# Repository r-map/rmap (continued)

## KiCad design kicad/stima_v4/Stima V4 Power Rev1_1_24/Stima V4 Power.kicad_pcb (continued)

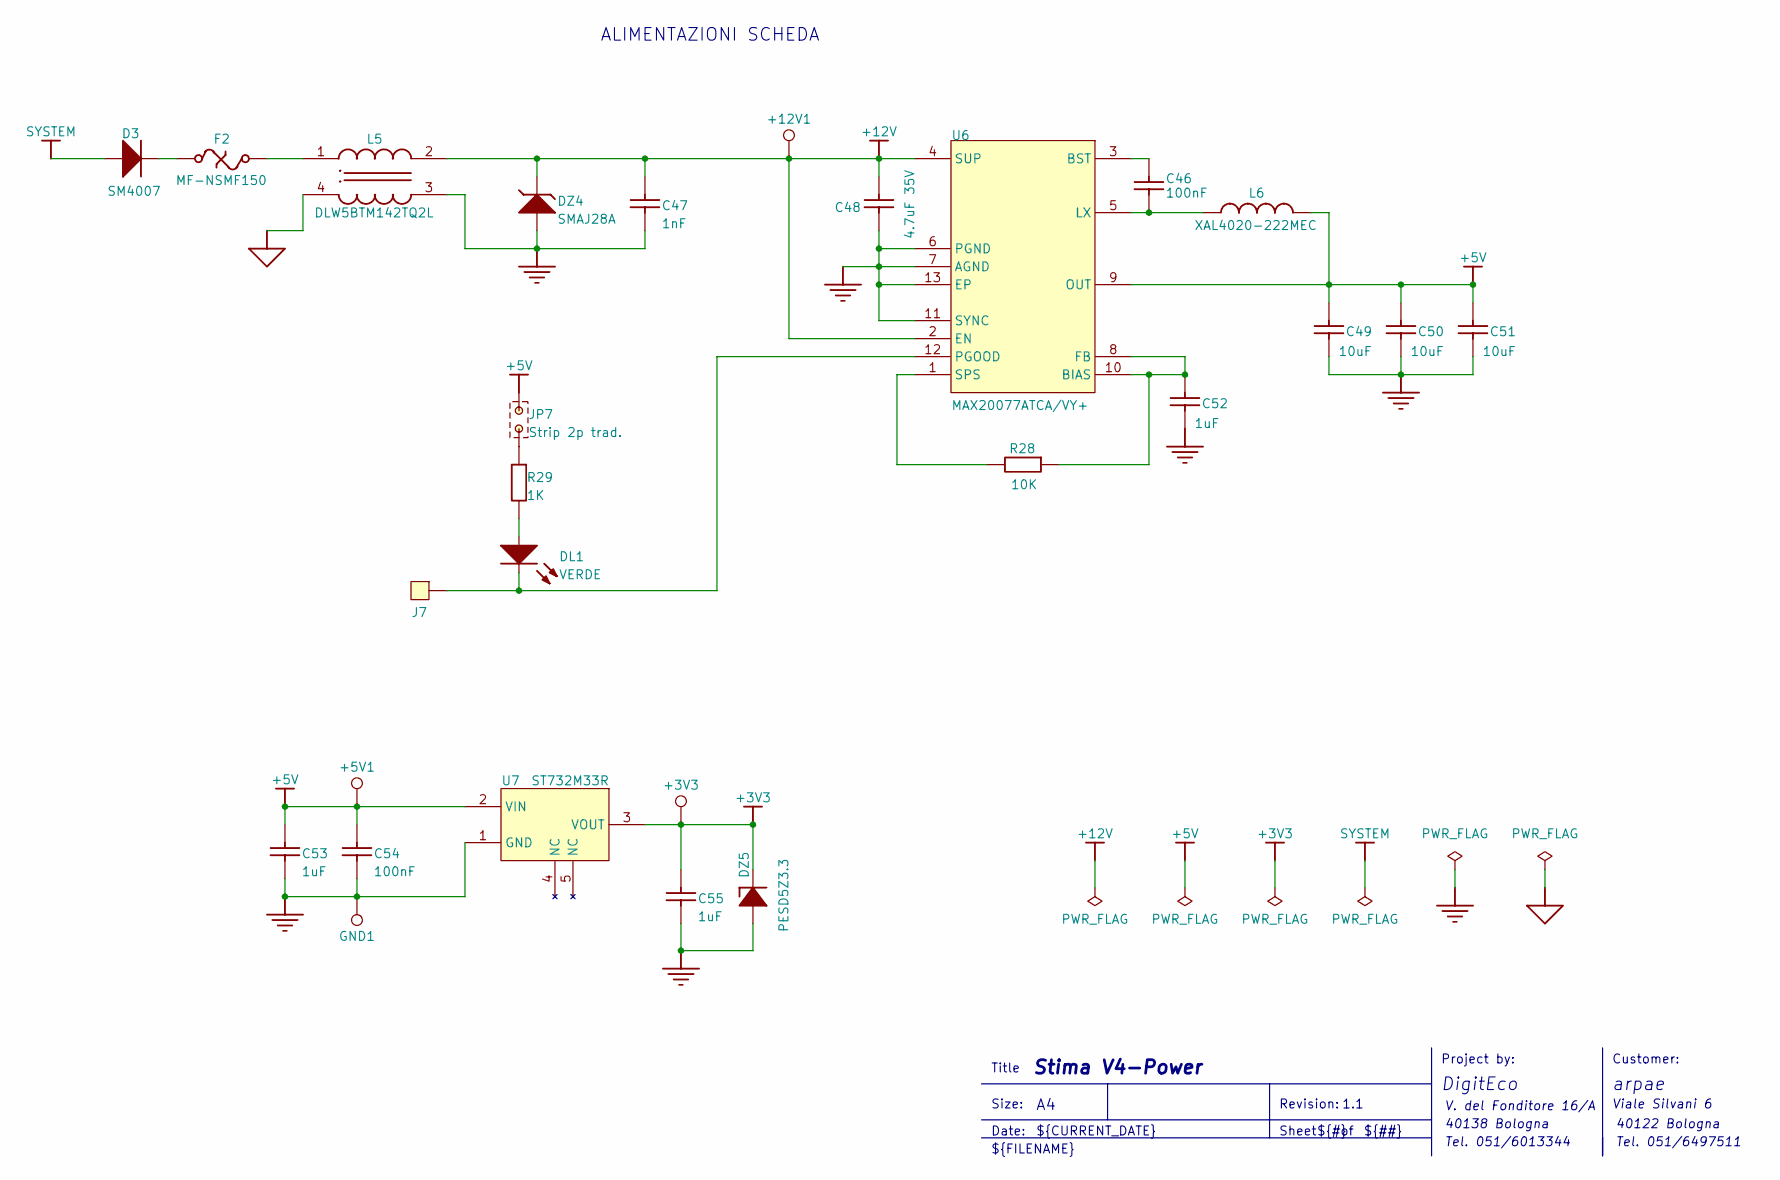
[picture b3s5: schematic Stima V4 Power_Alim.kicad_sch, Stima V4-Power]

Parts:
+3V3, +5V1, +12V1: TestPoint; TP
C46, C54: 100nF; 0603; VOLTAGE 50V
C47: 1nF; 0603; VOLTAGE 50V
C48: 4.7uF 35V; 1206; VOLTAGE 35V
C49, C50, C51: 10uF; 0603; VOLTAGE 20V
C52: 1uF; 0805; VOLTAGE 20V
C53, C55: 1uF; 0603; VOLTAGE 20V
D3: SM4007; QMELFD
DL1: VERDE; 0805-led
DZ4: SMAJ28A; SMA
DZ5: PESD5Z3.3; SOD 523(SC-79)
F2: MF-NSMF150; 1206
GND1: TestPoint; TP
J7: VIAS1; VIAS0_8
JP7: Strip 2p trad.; STRIP2P
L5: DLW5BTM142TQ2L; FILTRO DLW5B MIO
L6: XAL4020-222MEC; COIL COILCRAFT XAL4020-MIO
R28: 10K; 0603
R29: 1K; 0805
U6: MAX20077ATCA/VY+; TDFN 12L MIO
U7: ST732M33R; SOT23_5

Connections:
+3V3: +3V3.1, C55.1, DZ5.1 (K), U7.3 (VOUT); also elsewhere on the board
+5V: +5V1.1, C49.2, C50.2, C51.2, C53.1, C54.1, JP7.1, L6.2, U6.9 (OUT), U7.2 (VIN); also elsewhere on the board
+12V: +12V1.1, C47.1, C48.1, DZ4.1 (K), L5.2, U6.2 (EN), U6.4 (SUP); also elsewhere on the board
+AL: D3.2 (A); also elsewhere on the board
GND: C47.2, C48.2, C49.1, C50.1, C51.1, C52.1, C53.2, C54.2, C55.2, DZ4.2 (A), DZ5.2 (A), GND1.1, L5.3, U6.6 (PGND), U6.7 (AGND), U6.11 (SYNC), U6.13 (EP), U7.1 (GND); also elsewhere on the board
unnamed: D3.1 (K), F2.1
unnamed: DL1.2 (A), R29.1
unnamed: DL1.1 (K), J7.1, U6.12 (PGOOD)
unnamed: F2.2, L5.1
unnamed: JP7.2, R29.2
unnamed: C52.2, R28.2, U6.8 (FB), U6.10 (BIAS)
unnamed: C46.1, U6.3 (BST)
unnamed: C46.2, L6.1, U6.5 (LX)
unnamed: R28.1, U6.1 (SPS)

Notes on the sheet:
DigitEco
${#}
${FILENAME}
Sheet
arpae
40138 Bologna
Viale Silvani 6
Tel. 051/6497511
Customer:
Date:
Revision:
40122 Bologna
V. del Fonditore 16/A
${##}
Project by:
1.1
Tel. 051/6013344
${CURRENT_DATE}
Title
ALIMENTAZIONI SCHEDA
${TITLE}
Size:

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
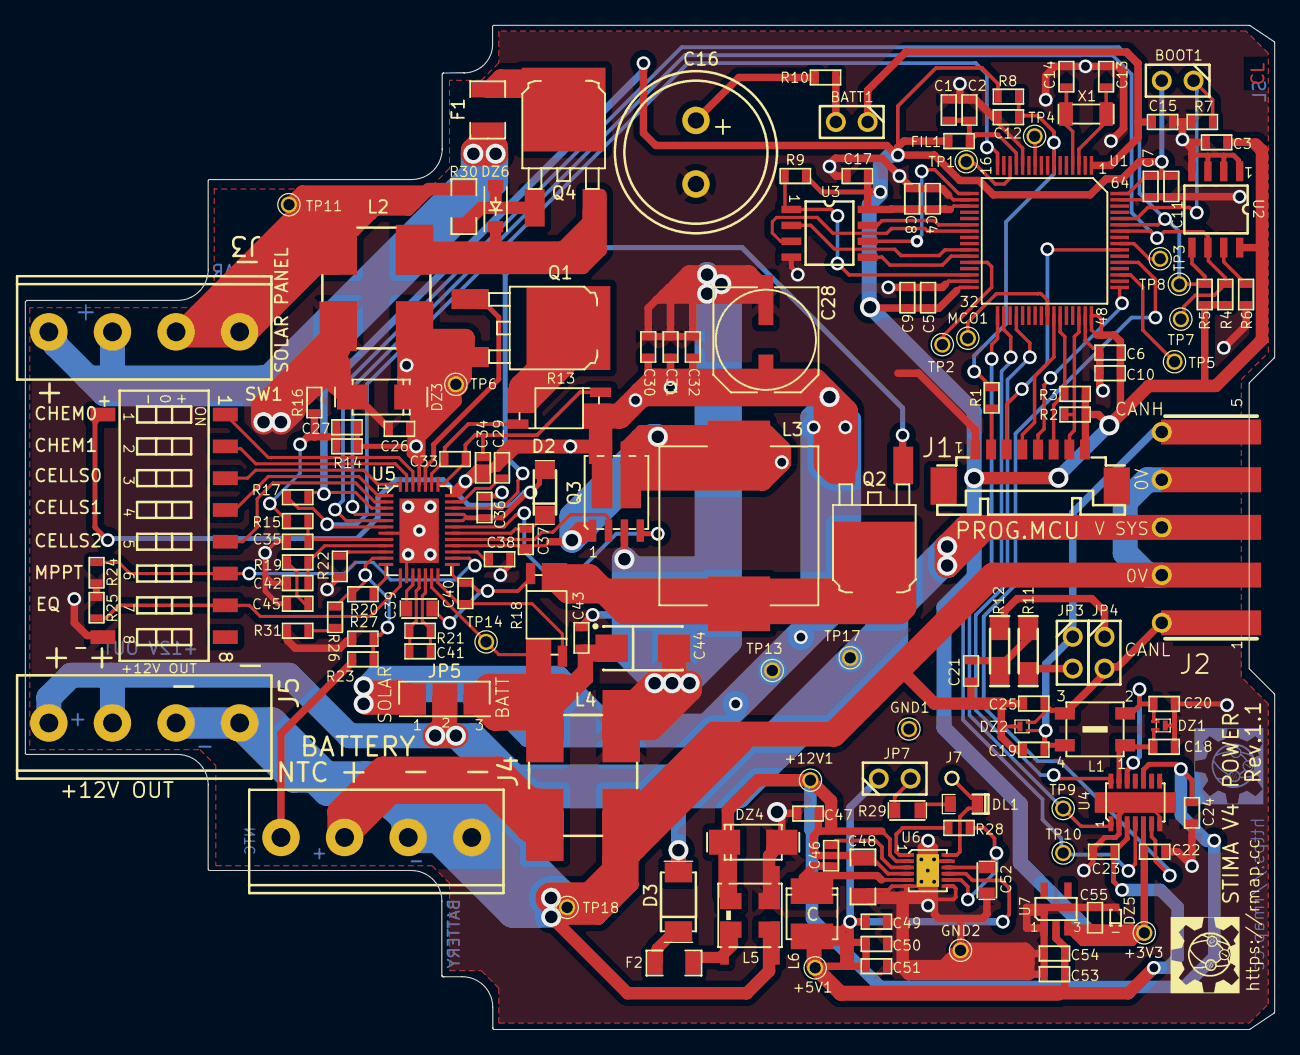
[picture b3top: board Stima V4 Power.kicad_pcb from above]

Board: 4 copper layers, 99.8 x 80.2 mm, 150 parts (0 on the bottom side), 99 nets.

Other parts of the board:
BATT1: Strip 2p PTH; STRIP2P
BOOT1: Strip 2p PTH; STRIP2P
J2: 5P BUS; CONTATTI5

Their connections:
+3V3: BOOT1.2; also elsewhere on the board
+AL: J2.3; also elsewhere on the board
/Stima V4 Power_Can/CANH: J2.5; also elsewhere on the board
unnamed 25: BATT1.2; also elsewhere on the board
unnamed 59: BOOT1.1; also elsewhere on the board
unnamed 60: BATT1.1; also elsewhere on the board

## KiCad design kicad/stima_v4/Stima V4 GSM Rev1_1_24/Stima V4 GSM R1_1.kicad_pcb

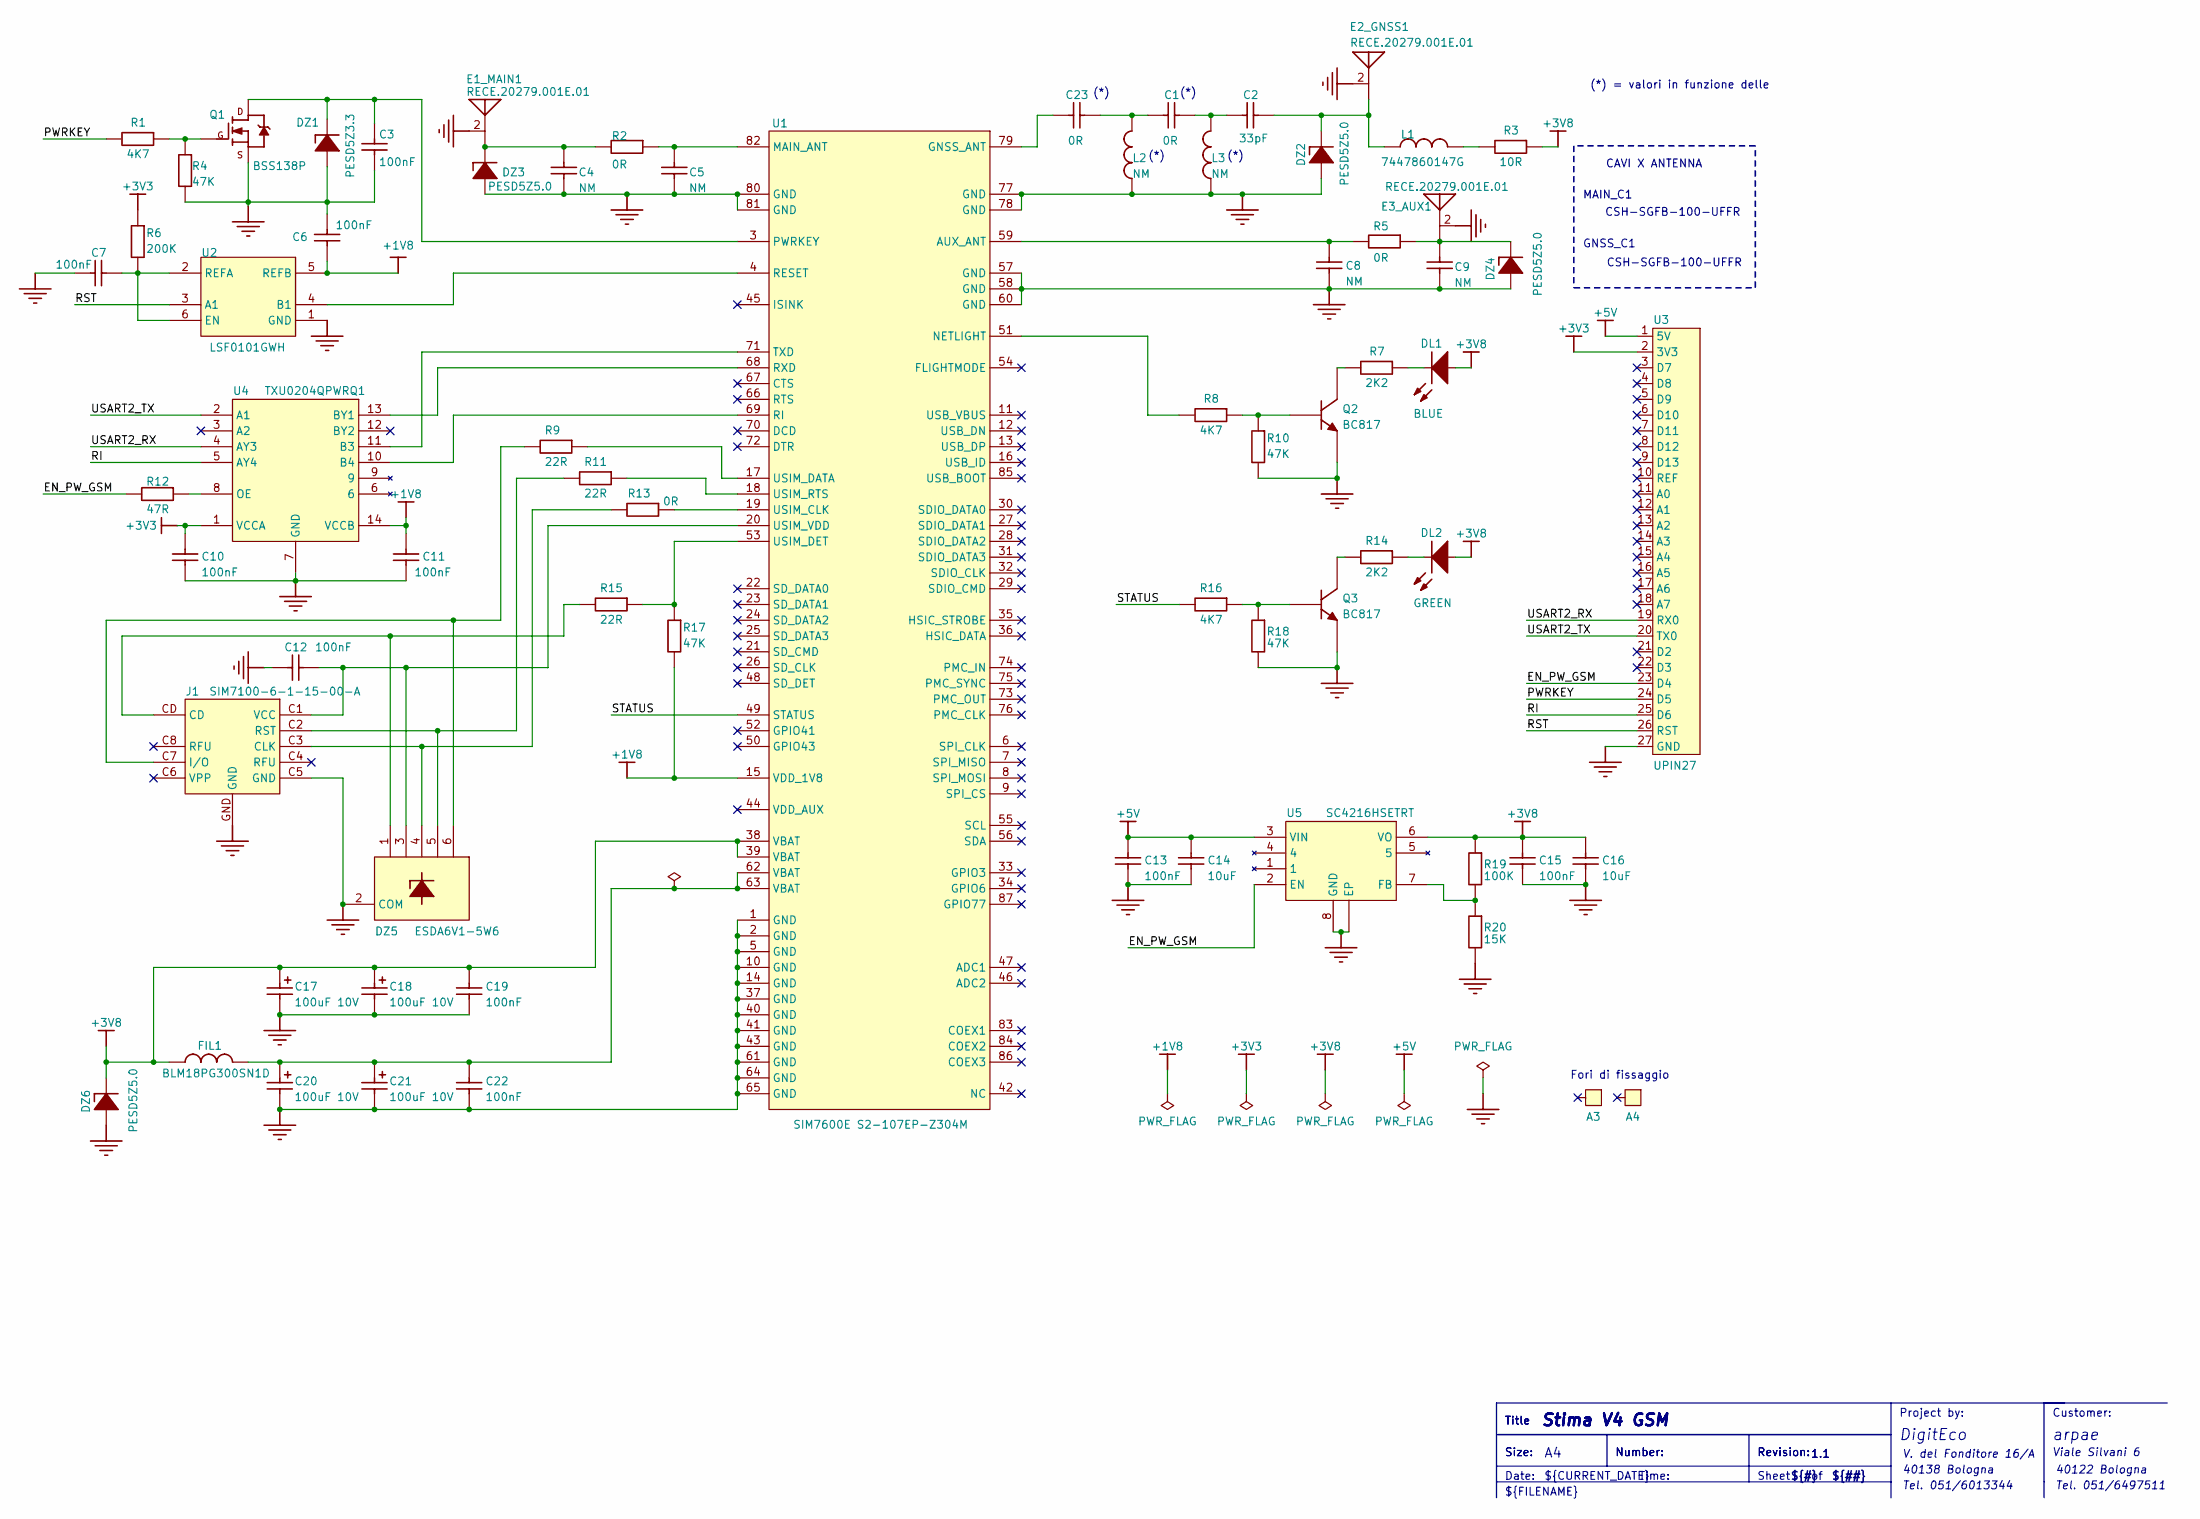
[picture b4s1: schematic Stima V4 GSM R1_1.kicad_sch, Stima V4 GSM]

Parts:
A3, A4: ViteDado; ViteDado4
C1, C23: 0R; 0603; VOLTAGE 20V
C2: 33pF; 0603; VOLTAGE 20V
C3, C6, C7, C13, C15, C19, C22: 100nF; 0603; VOLTAGE 20V
C4, C5, C8, C9: NM; 0603; VOLTAGE 20V
C10, C11, C12: 100nF; 0603; VOLTAGE 50V
C14, C16: 10uF; 0603; VOLTAGE 16V
C17, C18, C20, C21: 100uF 10V; Case B-TC3528-1411; VOLTAGE 10V
DL1: BLUE; 0805-led
DL2: GREEN; 0805-led
DZ1: PESD5Z3.3; SOD 523(SC-79)
DZ2, DZ3, DZ4, DZ6: PESD5Z5.0; SOD 523(SC-79)
DZ5: ESDA6V1-5W6; SOT363(SC70)
E1_MAIN1, E2_GNSS1, E3_AUX1: RECE.20279.001E.01; CONN_ANTENNA_SMD
FIL1: BLM18PG300SN1D; 0603
J1: SIM7100-6-1-15-00-A; SIM CARD MICRO
L1: 7447860147G; 0603
L2, L3: NM; 0603
Q1: BSS138P; SOT23
Q2, Q3: BC817; SOT23
R1, R8, R16: 4K7; 0603
R2, R5, R13: 0R; 0603
R3: 10R; 0603
R4, R10, R17, R18: 47K; 0603
R6: 200K; 0603
R7, R14: 2K2; 0603
R9, R11, R15: 22R; 0603
R12: 47R; 0603
R19: 100K; 0603
R20: 15K; 0603
U1: SIM7600E S2-107EP-Z304M; SIM7600
U2: LSF0101GWH; SOT363(SC70)
U3: UPIN27; UPIN27_OK
U4: TXU0204QPWRQ1; TSSOP14
U5: SC4216HSETRT; SO8-EDP-2 MIO

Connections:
+1V8: C6.1, C11.1, R17.2, U1.15 (VDD_1V8), U2.5 (REFB), U4.14 (VCCB)
+3V3: C10.1, R6.2, U3.2 (3V3), U4.1 (VCCA)
+3V8: C15.1, C16.1, C17.1, C18.1, C19.1, DL1.2 (A), DL2.2 (A), DZ6.1 (K), FIL1.1, R3.1, R19.2, U1.38 (VBAT), U1.39 (VBAT), U5.6 (VO)
+5V: C13.1, C14.1, U3.1 (5V), U5.3 (VIN)
/EN_PW_GSM: R12.2, U3.23 (D4), U5.2 (EN)
/PWRKEY: R1.2, U3.24 (D5)
/RI: U3.25 (D6), U4.5 (AY4)
/RST: U2.3 (A1), U3.26 (RST)
/STATUS: R16.2, U1.49 (STATUS)
/USART2_RX: U3.19 (RX0), U4.4 (AY3)
/USART2_TX: U3.20 (TX0), U4.2 (A1)
GND: C3.2, C4.2, C5.2, C6.2, C7.2, C8.2, C9.2, C10.2, C11.2, C12.2, C13.2, C14.2, C15.2, C16.2, C17.2, C18.2, C19.2, C20.2, C21.2, C22.2, DZ1.2 (A), DZ2.2 (A), DZ3.2 (A), DZ4.2 (A), DZ5.2 (COM), DZ6.2 (A), E1_MAIN1.2, E2_GNSS1.2, E3_AUX1.2, J1.C5 (GND), J1.GND, L2.1, L3.1, Q1.2 (S), Q2.2 (E), Q3.2 (E), R4.1, R10.1, R18.1, R20.1, U1.1 (GND), U1.2 (GND), U1.5 (GND), U1.10 (GND), U1.14 (GND), U1.37 (GND), U1.40 (GND), U1.41 (GND), U1.43 (GND), U1.57 (GND), U1.58 (GND), U1.60 (GND), U1.61 (GND), U1.64 (GND), U1.65 (GND), U1.77 (GND), U1.78 (GND), U1.80 (GND), U1.81 (GND), U2.1 (GND), U3.27 (GND), U4.7 (GND), U5.8 (GND), U5.9 (EP)
unnamed: C1.1, C23.2, L2.2
unnamed: C1.2, C2.1, L3.2
unnamed: C20.1, C21.1, C22.1, FIL1.2, U1.62 (VBAT), U1.63 (VBAT)
unnamed: DL1.1 (K), R7.1
unnamed: DL2.1 (K), R14.1
unnamed: C3.1, DZ1.1 (K), Q1.3 (D), U1.3 (PWRKEY)
unnamed: C2.2, DZ2.1 (K), E2_GNSS1.1 (A), L1.1
unnamed: C4.1, DZ3.1 (K), E1_MAIN1.1 (A), R2.2
unnamed: C9.1, DZ4.1 (K), E3_AUX1.1 (A), R5.1
unnamed: DZ5.1 (TVS1), J1.CD, R15.2
unnamed: C12.1, DZ5.3 (TVS2), J1.C1 (VCC), U1.20 (USIM_VDD)
unnamed: DZ5.4 (TVS3), J1.C3 (CLK), R13.2
unnamed: DZ5.5 (TVS4), J1.C2 (RST), R11.2
unnamed: DZ5.6 (TVS5), J1.C7 (I/O), R9.2
unnamed: L1.2, R3.2
unnamed: Q1.1 (G), R1.1, R4.2
unnamed: Q2.1 (B), R8.1, R10.2
unnamed: Q2.3 (C), R7.2
unnamed: Q3.1 (B), R16.1, R18.2
unnamed: Q3.3 (C), R14.2
unnamed: C8.1, R5.2, U1.59 (AUX_ANT)
unnamed: C23.1, U1.79 (GNSS_ANT)
unnamed: C5.1, R2.1, U1.82 (MAIN_ANT)
unnamed: R8.2, U1.51 (NETLIGHT)
unnamed: U1.4 (RESET), U2.4 (B1)
unnamed: U1.69 (RI), U4.10 (B4)
unnamed: U1.68 (RXD), U4.13 (BY1)
unnamed: U1.71 (TXD), U4.11 (B3)
unnamed: R13.1, U1.19 (USIM_CLK)
unnamed: R9.1, U1.17 (USIM_DATA)
unnamed: R15.1, R17.1, U1.53 (USIM_DET)
unnamed: R11.1, U1.18 (USIM_RTS)
unnamed: C7.1, R6.1, U2.2 (REFA), U2.6 (EN)
unnamed: R12.1, U4.8 (OE)
unnamed: R19.1, R20.2, U5.7 (FB)

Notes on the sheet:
Title
Project by:
Number:
Viale Silvani 6
Revision:
Fori di fissaggio
1.1
Tel. 051/6013344
(*) = valori in funzione delle
40138 Bologna
${CURRENT_DATE}
CAVI X ANTENNA
Size:
${##}
(*)
MAIN_C1
Date:
${FILENAME}
${TITLE}
CSH-SGFB-100-UFFR
Tel. 051/6497511
Time:
GNSS_C1
Customer:
40122 Bologna
arpae
Sheet
V. del Fonditore 16/A
DigitEco
${#}

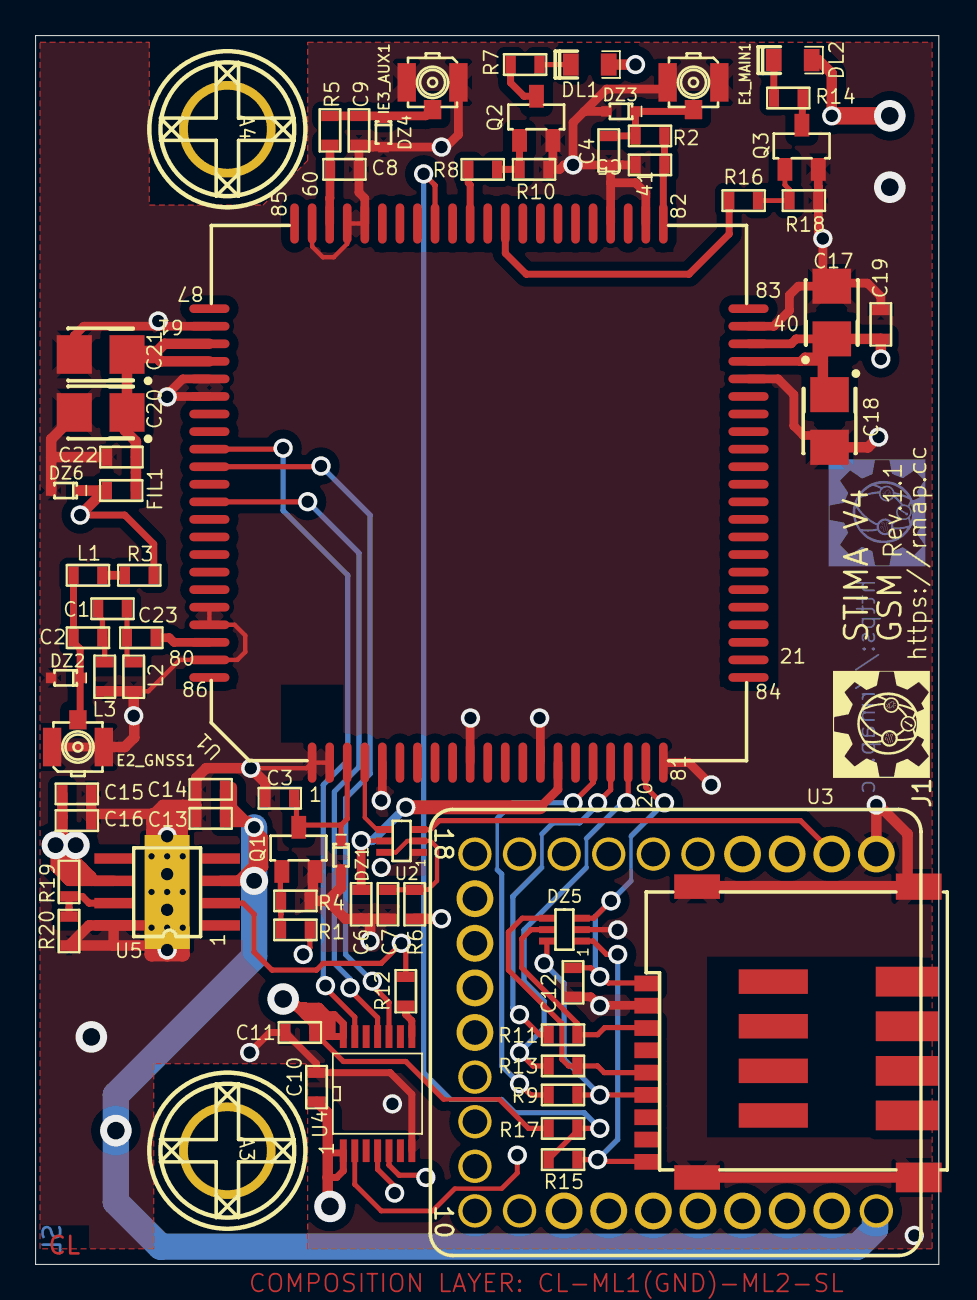
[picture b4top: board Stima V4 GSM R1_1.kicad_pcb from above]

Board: 4 copper layers, 51.4 x 70.0 mm, 69 parts (0 on the bottom side), 47 nets.

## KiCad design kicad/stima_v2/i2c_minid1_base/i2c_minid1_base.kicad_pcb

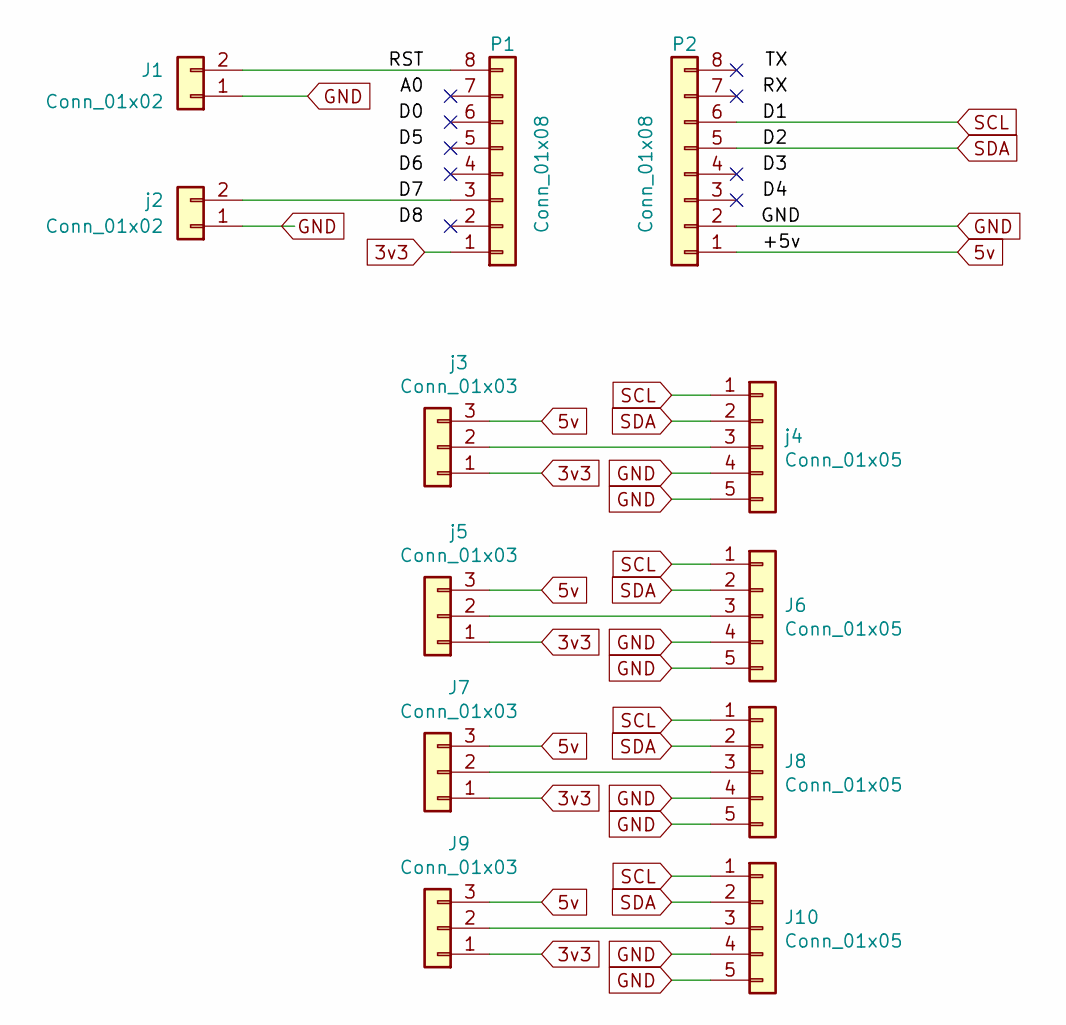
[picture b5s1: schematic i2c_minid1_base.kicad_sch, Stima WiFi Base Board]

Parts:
J1: Conn_01x02; PinHeader_1x02_P2.54mm_Vertical
J6, J8, J10: Conn_01x05; Molex_KK-254_AE-6410-05A_1x05_P2.54mm_Vertical
J7, J9: Conn_01x03; PinHeader_1x03_P2.54mm_Vertical
P1, P2: Conn_01x08; PinHeader_1x08_P2.54mm_Vertical
j2: Conn_01x02; PinHeader_1x03_P2.54mm_Vertical
j3, j5: Conn_01x03; PinHeader_1x03_P2.54mm_Vertical
j4: Conn_01x05; Molex_KK-254_AE-6410-05A_1x05_P2.54mm_Vertical

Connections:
3v3: J7.1, J9.1, P1.1, j3.1, j5.1
5v: J7.3, J9.3, P2.1, j3.3, j5.3
/D7: P1.3, j2.2
/RST: J1.2, P1.8
GND: J1.1, J6.4, J6.5, J8.4, J8.5, J10.4, J10.5, P2.2, j2.1, j4.4, j4.5
unnamed: J6.3, j5.2
unnamed: J7.2, J8.3
unnamed: J9.2, J10.3
unnamed: j3.2, j4.3
SCL: J6.1, J8.1, J10.1, P2.6, j4.1
SDA: J6.2, J8.2, J10.2, P2.5, j4.2

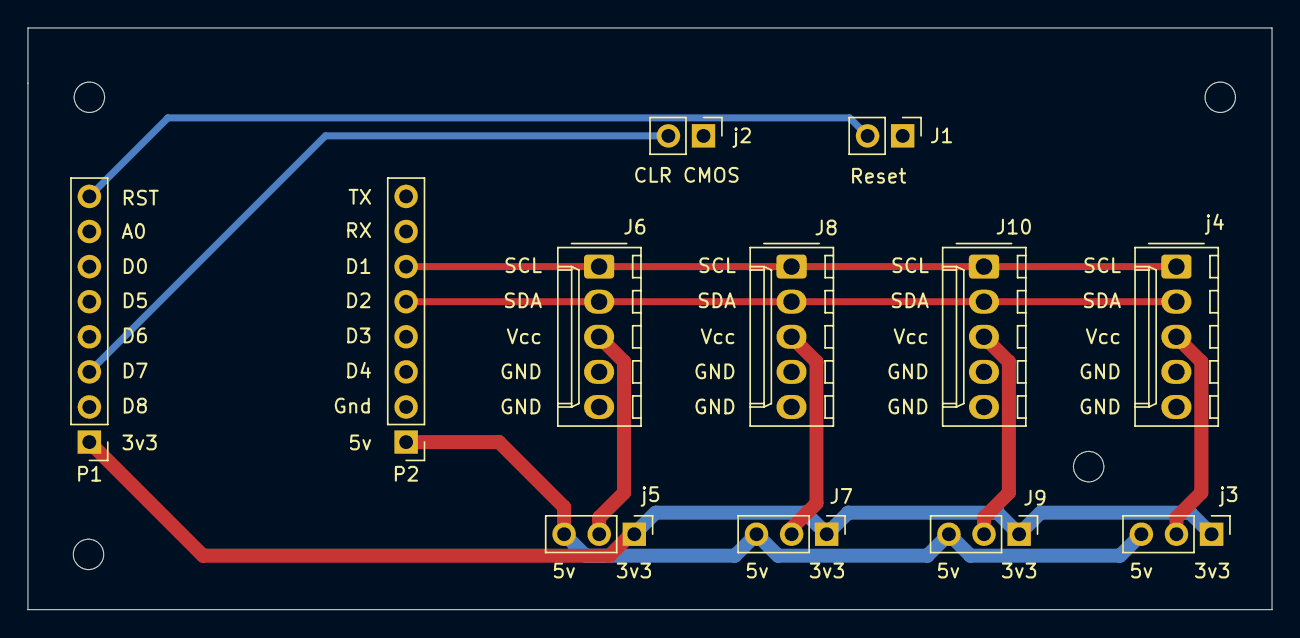
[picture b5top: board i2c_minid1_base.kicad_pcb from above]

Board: 2 copper layers, 90.0 x 42.1 mm, 12 parts (0 on the bottom side), 11 nets.

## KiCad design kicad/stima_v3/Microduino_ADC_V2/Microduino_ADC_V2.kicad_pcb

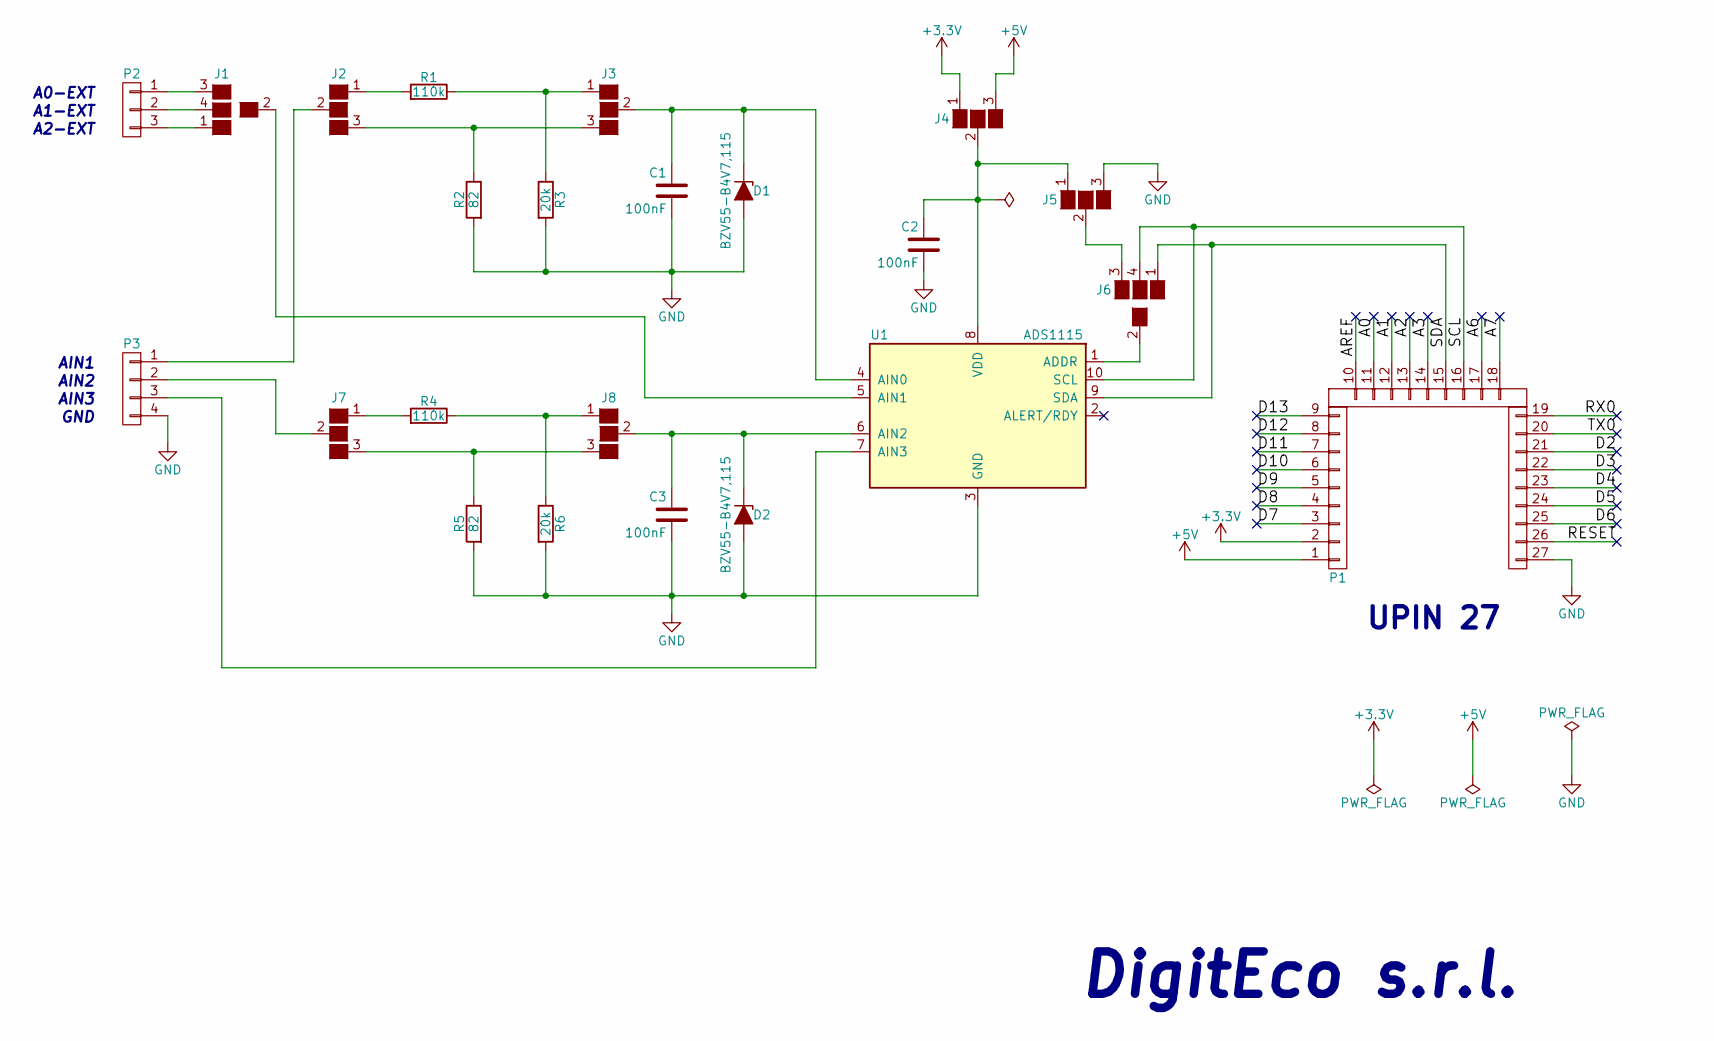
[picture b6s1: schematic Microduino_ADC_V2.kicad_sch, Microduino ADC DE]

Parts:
C1, C2, C3: 100nF; C_0805
D1, D2: BZV55-B4V7,115; D_MiniMELF
J1, J6: GS4_b; GS4
J2, J3, J4, J5, J7, J8: GS3
P1: CONN_1x27; Upin_27
P2: CONN_01X03; Pin_Header_Straight_1x03_Pitch2.54mm
P3: CONN_01X04; WHURT_4pin_90°_61900411021
R1, R4: 110k; R_0805
R2, R5: 82; R_0805
R3, R6: 20k; R_0805
U1: ADS1115; MSOP-10_3x3mm_Pitch0.5mm

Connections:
+3V3: J4.1 (G1), P1.2
+5V: J4.3 (G3), P1.1
/A0: P1.11
/A1: P1.12
/A2: P1.13
/A3: P1.14
/A6: P1.17
/A7: P1.18
/AREF: P1.10
/D2: P1.21
/D3: P1.22
/D4: P1.23
/D5: P1.24
/D6: P1.25
/D7: P1.3
/D8: P1.4
/D9: P1.5
/D10: P1.6
/D11: P1.7
/D12: P1.8
/D13: P1.9
/RESET: P1.26
/RX0: P1.19
/SCL: J6.4 (G3), P1.16, U1.10 (SCL)
/SDA: J6.1 (G1), P1.15, U1.9 (SDA)
/TX0: P1.20
GND: C1.2, C2.2, C3.2, D1.2 (A), D2.2 (A), J5.3 (G3), P1.27, P3.4, R2.2, R3.2, R5.2, R6.2, U1.3 (GND)
unnamed: C1.1, D1.1 (K), J3.2 (G2), U1.4 (AIN0)
unnamed: C2.1, J4.2 (G2), J5.1 (G1), U1.8 (VDD)
unnamed: C3.1, D2.1 (K), J8.2 (G2), U1.6 (AIN2)
unnamed: J1.1 (G1), P2.3
unnamed: J1.2 (G2), U1.5 (AIN1)
unnamed: J1.3 (G4), P2.1
unnamed: J1.4 (G3), P2.2
unnamed: J2.1 (G1), R1.2
unnamed: J2.2 (G2), P3.1
unnamed: J2.3 (G3), J3.3 (G3), R2.1
unnamed: J3.1 (G1), R1.1, R3.1
unnamed: J5.2 (G2), J6.3 (G4)
unnamed: J6.2 (G2), U1.1 (ADDR)
unnamed: J7.1 (G1), R4.2
unnamed: J7.2 (G2), P3.2
unnamed: J7.3 (G3), J8.3 (G3), R5.1
unnamed: J8.1 (G1), R4.1, R6.1
unnamed: P3.3, U1.7 (AIN3)

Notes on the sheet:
AIN3
A0-EXT
A2-EXT
A1-EXT
UPIN 27
DigitEco s.r.l.
GND
AIN2
AIN1

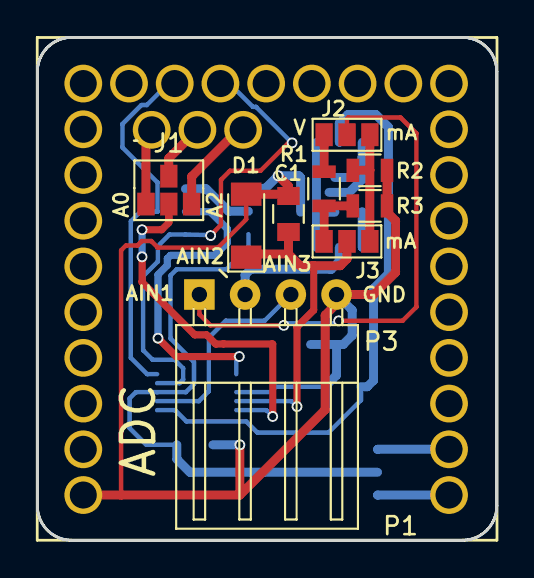
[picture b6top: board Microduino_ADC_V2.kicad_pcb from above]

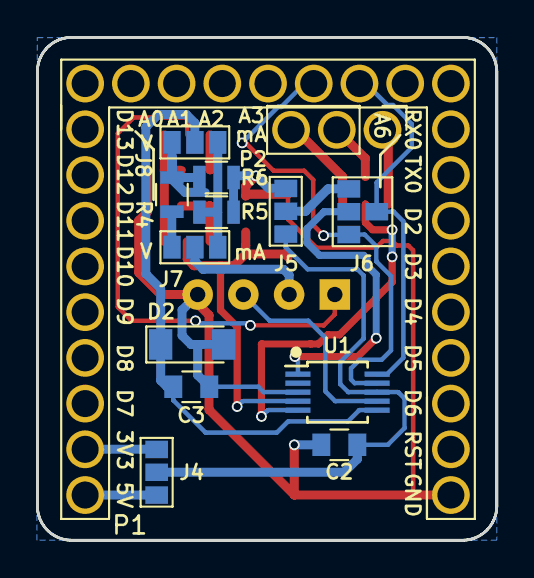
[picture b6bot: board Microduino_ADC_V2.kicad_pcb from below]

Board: 2 copper layers, 25.5 x 27.9 mm, 23 parts (14 on the bottom side), 23 nets.

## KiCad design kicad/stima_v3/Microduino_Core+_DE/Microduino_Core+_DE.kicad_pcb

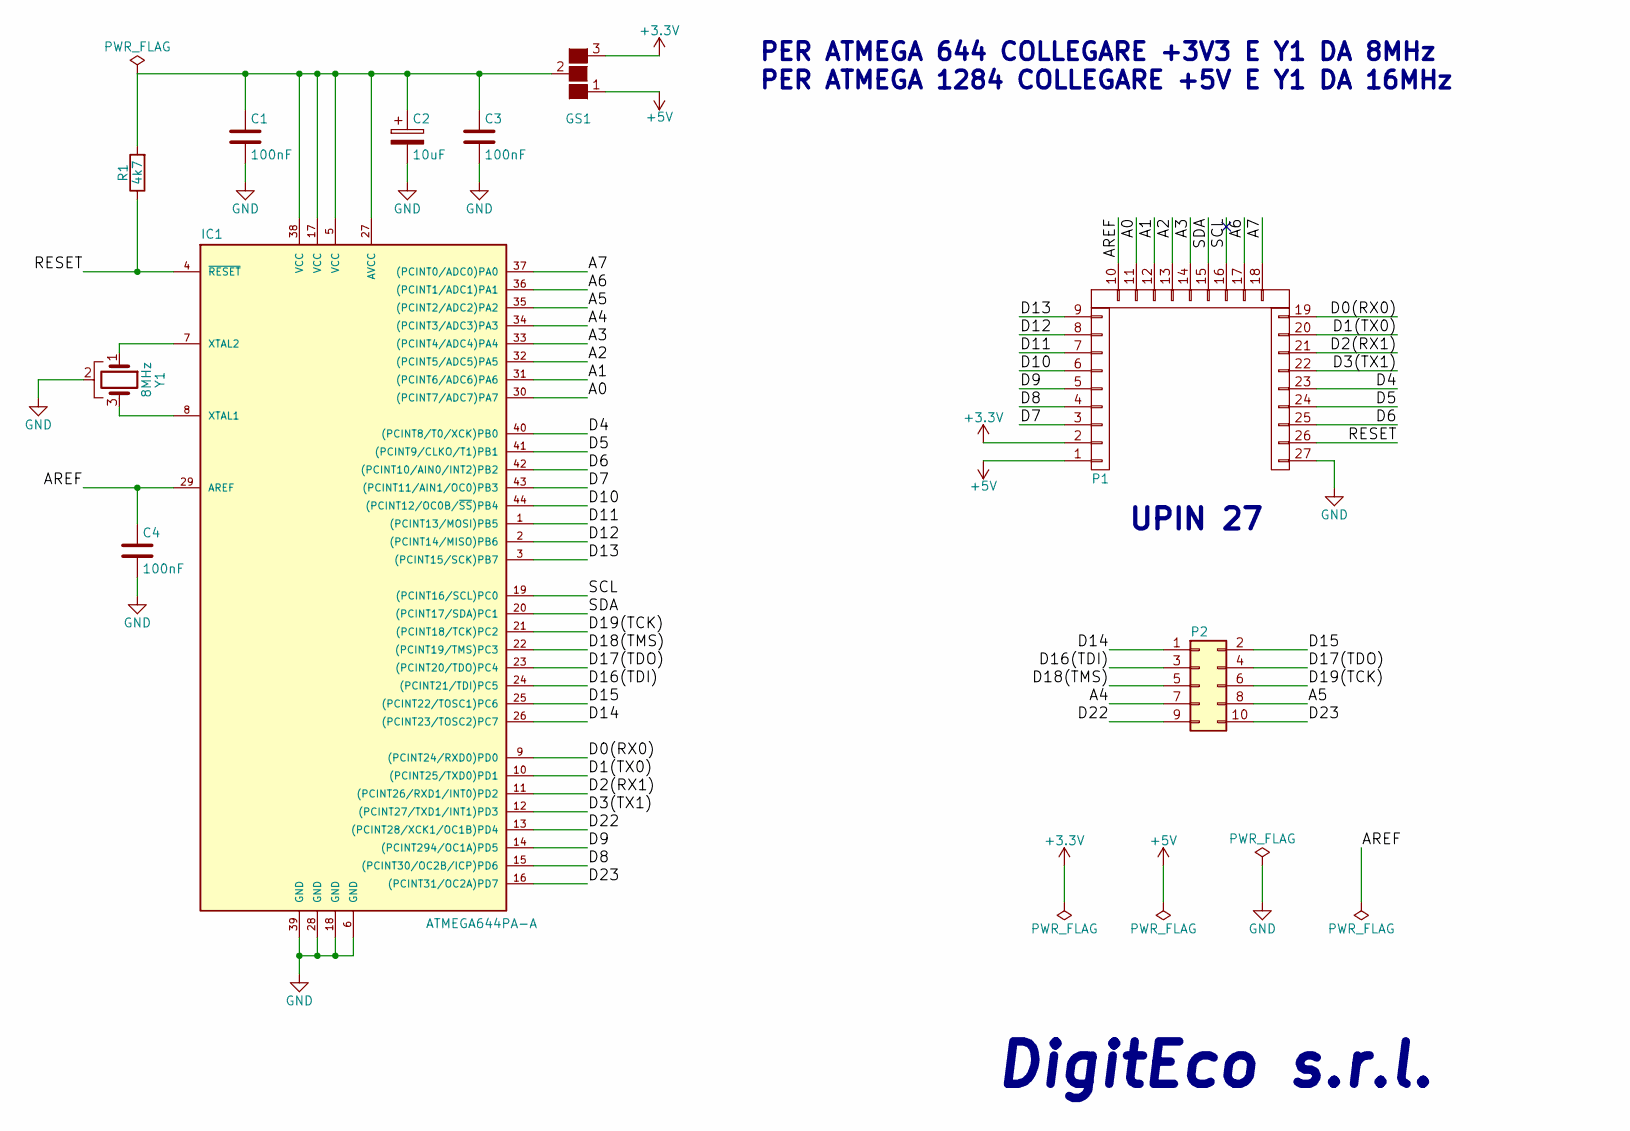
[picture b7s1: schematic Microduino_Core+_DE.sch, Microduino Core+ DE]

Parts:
C1: 100nF; C_0805_315°
C2: 10uF; CP_Tantalum_Case-B_EIA-3528-21_Reflow
C3, C4: 100nF; C_0805
GS1: GS3
IC1: ATMEGA644PA-A; TQFP-44_10x10mm_Pitch0.8mm
P1: CONN_1x27; Upin_27
P2: CONN_02X05; Pin_Header_Straight_2x05_Pitch2.54mm
R1: 4k7; R_0805
Y1: 8MHz; Resonator_SMD_muRata_CST-3pin_3.2x1.3mm

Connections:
+3V3: GS1.3 (G3), P1.2
+5V: GS1.1 (G1), P1.1
/A0: IC1.30 ((PCINT7/ADC7)PA7), P1.11
/A1: IC1.31 ((PCINT6/ADC6)PA6), P1.12
/A2: IC1.32 ((PCINT5/ADC5)PA5), P1.13
/A3: IC1.33 ((PCINT4/ADC4)PA4), P1.14
/A4: IC1.34 ((PCINT3/ADC3)PA3), P2.7
/A5: IC1.35 ((PCINT2/ADC2)PA2), P2.8
/A6: IC1.36 ((PCINT1/ADC1)PA1), P1.17
/A7: IC1.37 ((PCINT0/ADC0)PA0), P1.18
/AREF: C4.1, IC1.29 (AREF), P1.10
/D0(RX0): IC1.9 ((PCINT24/RXD0)PD0), P1.19
/D1(TX0): IC1.10 ((PCINT25/TXD0)PD1), P1.20
/D2(RX1): IC1.11 ((PCINT26/RXD1/INT0)PD2), P1.21
/D3(TX1): IC1.12 ((PCINT27/TXD1/INT1)PD3), P1.22
/D4: IC1.40 ((PCINT8/T0/XCK)PB0), P1.23
/D5: IC1.41 ((PCINT9/CLKO/T1)PB1), P1.24
/D6: IC1.42 ((PCINT10/AIN0/INT2)PB2), P1.25
/D7: IC1.43 ((PCINT11/AIN1/OC0)PB3), P1.3
/D8: IC1.15 ((PCINT30/OC2B/ICP)PD6), P1.4
/D9: IC1.14 ((PCINT294/OC1A)PD5), P1.5
/D10: IC1.44 ((PCINT12/OC0B/~SS~)PB4), P1.6
/D11: IC1.1 ((PCINT13/MOSI)PB5), P1.7
/D12: IC1.2 ((PCINT14/MISO)PB6), P1.8
/D13: IC1.3 ((PCINT15/SCK)PB7), P1.9
/D14: IC1.26 ((PCINT23/TOSC2)PC7), P2.1
/D15: IC1.25 ((PCINT22/TOSC1)PC6), P2.2
/D16(TDI): IC1.24 ((PCINT21/TDI)PC5), P2.3
/D17(TDO): IC1.23 ((PCINT20/TDO)PC4), P2.4
/D18(TMS): IC1.22 ((PCINT19/TMS)PC3), P2.5
/D19(TCK): IC1.21 ((PCINT18/TCK)PC2), P2.6
/D22: IC1.13 ((PCINT28/XCK1/OC1B)PD4), P2.9
/D23: IC1.16 ((PCINT31/OC2A)PD7), P2.10
/RESET: IC1.4 (~RESET), P1.26, R1.1
/SCL: IC1.19 ((PCINT16/SCL)PC0), P1.16
/SDA: IC1.20 ((PCINT17/SDA)PC1), P1.15
GND: C1.2, C2.2, C3.2, C4.2, IC1.6 (GND), IC1.18 (GND), IC1.28 (GND), IC1.39 (GND), P1.27, Y1.2
unnamed: C1.1, C2.1, C3.1, GS1.2 (G2), IC1.5 (VCC), IC1.17 (VCC), IC1.27 (AVCC), IC1.38 (VCC), R1.2
unnamed: IC1.7 (XTAL2), Y1.1
unnamed: IC1.8 (XTAL1), Y1.3

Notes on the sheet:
UPIN 27
DigitEco s.r.l.
PER ATMEGA 644 COLLEGARE +3V3 E Y1 DA 8MHz PER ATMEGA 1284 COLLEGARE +5V E Y1 DA 16MHz

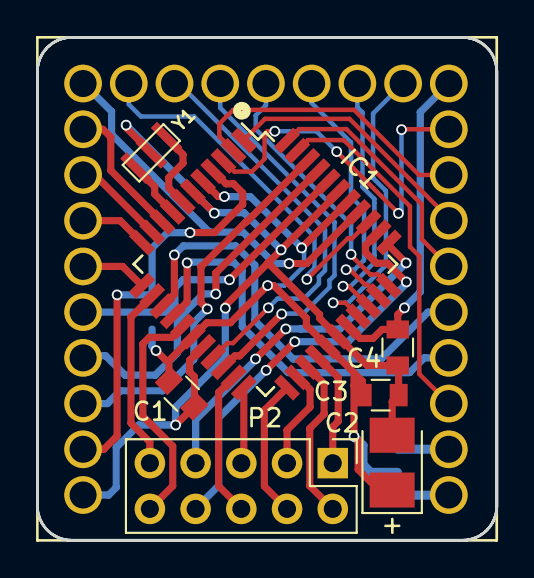
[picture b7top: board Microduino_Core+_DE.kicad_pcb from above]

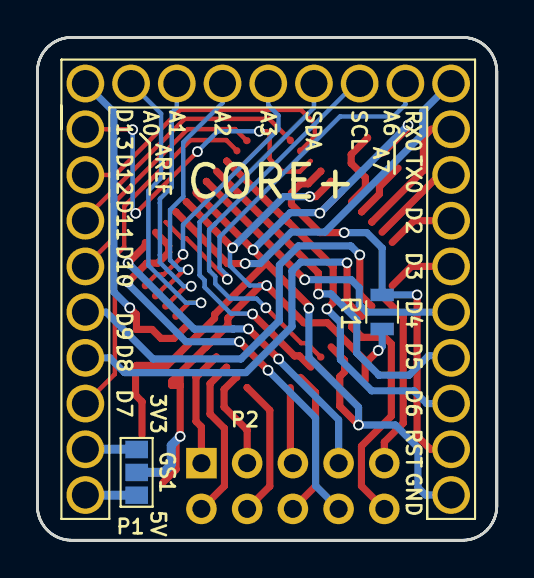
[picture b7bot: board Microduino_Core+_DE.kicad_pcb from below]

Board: 2 copper layers, 25.5 x 27.9 mm, 10 parts (3 on the bottom side), 40 nets.
